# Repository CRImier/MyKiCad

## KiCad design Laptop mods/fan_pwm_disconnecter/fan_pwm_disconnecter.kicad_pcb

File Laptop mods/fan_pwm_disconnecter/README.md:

# Laptop fan PWM disconnecter

This is a board that allows you to run your laptop fans at full speed.
It is controlled by either a slide switch (included) or a toggle button..

It should be compatible with any kind of fan pinout. It has a slide switch attached that lets you test it the board,
and the switch board breaks off so you can place it somewhere where the switch will be accessible to you without disassembly,
using just two wires.

How to add this board to your laptop:

1) find out your fan's pinout. It's going to have 4 pins:
    - GND: ground
    - VCC: power
    - SENS: fan RPM signal output. We're not interested in this pin, it should just be passed through.
    - PWM: signal for fan speed control
2) jumper two-pin pads on the back that correspond to GND, VCC and SENS on the pinout. Leave the PWM pins un-jumpered.
3) connect the GND pad to the GND jumper pads
4) connect the VCC pad to the VCC jumper pads
5) connect the input PWM pad to the PWM jumper input pad
6) connect the output PWM pad to the PWM jumper output pad
7) Plug the fan into the board and plug the board into your laptop's motherboard
8) Test that everything works as intended
9) Break away the switch PCB
10) Position and fasten the main board inside the laptop's case - insulate the board with kapton tape, use double-sided tape or hotglue as needed
11) Position and fasten the switch board inside the laptop's case, the same way. You can put it e.g. under the RAM/HDD cover or behind the Kensington lock plate.
12) Use wires to connect the slide switch to the switch connector on the top of the board.

This repository also includes files for manufacturing a 2x9 panel.
Signal names are silkscreened on the board's bottom layer.

- PCB size: 36.25mm*8.25mm
- Layer count: 2

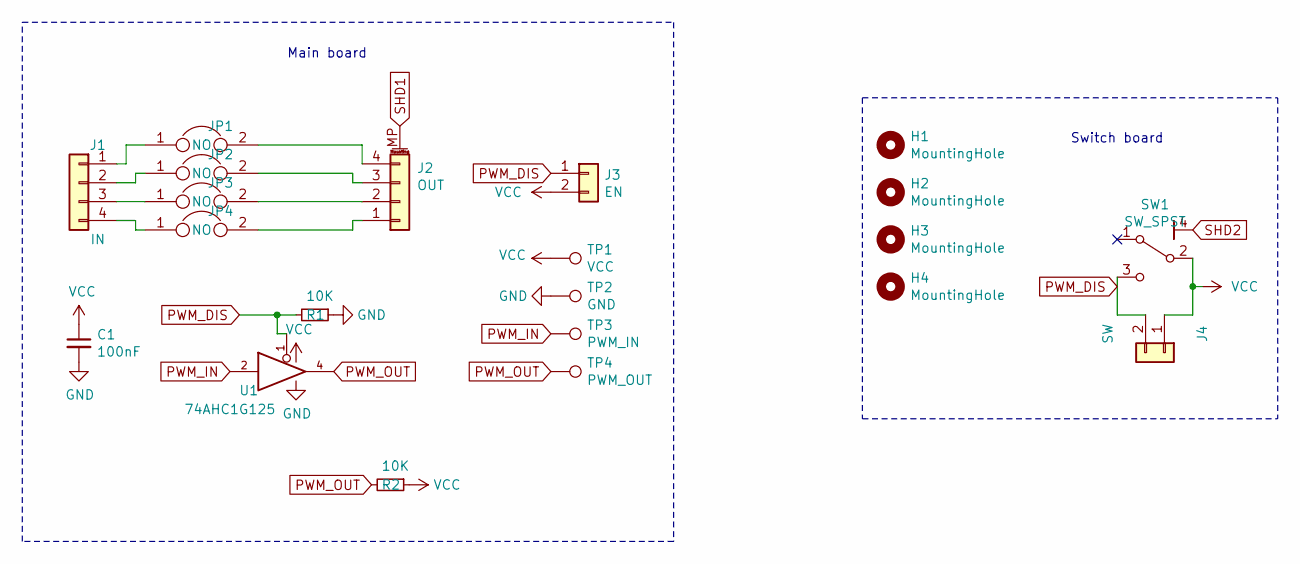
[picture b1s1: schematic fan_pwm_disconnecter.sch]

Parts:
C1: 100nF; C_0805_2012Metric_Pad1.15x1.40mm_HandSolder
H1, H2, H3, H4: MountingHole; MountingHole_2mm
J1: IN; PinHeader_1x04_P2.00mm_Vertical
J2: OUT; JST_SH_SM04B-SRSS-TB_1x04-1MP_P1.00mm_Horizontal
J3: EN; PinHeader_1x02_P2.00mm_Vertical
J4: SW; PinHeader_1x04_P2.00mm_Vertical
JP1, JP2, JP3, JP4: NO; SolderJumper-2_P1.3mm_Open_Pad1.0x1.0mm
R1, R2: 10K; R_0805_2012Metric_Pad1.15x1.40mm_HandSolder
SW1: SW_SPST; SW_SPDT_PCM12
TP1: VCC; TestPoint_Pad_1.0x1.0mm
TP2: GND; TestPoint_Pad_1.0x1.0mm
TP3: PWM_IN; TestPoint_Pad_1.0x1.0mm
TP4: PWM_OUT; TestPoint_Pad_1.0x1.0mm
U1: 74AHC1G125; SOT-353_SC-70-5_Handsoldering

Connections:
GND: C1.2, R1.1, TP2.1, U1.3 (GND)
unnamed: J1.1, JP1.1
unnamed: J1.2, JP2.1
unnamed: J1.3, JP3.1
unnamed: J1.4, JP4.1
unnamed: J2.1, JP4.2
unnamed: J2.2, JP3.2
unnamed: J2.3, JP2.2
unnamed: J2.4, JP1.2
PWM_DIS: J3.1, J4.2, R1.2, SW1.3 (C), U1.1
PWM_IN: TP3.1, U1.2
PWM_OUT: R2.2, TP4.1, U1.4
SHD1: J2.MP (MountPin)
SHD2: SW1.4 (SHD)
VCC: C1.1, J3.2, J4.1, R2.1, SW1.2 (B), TP1.1, U1.5 (VCC)

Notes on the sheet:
Main board
Switch board

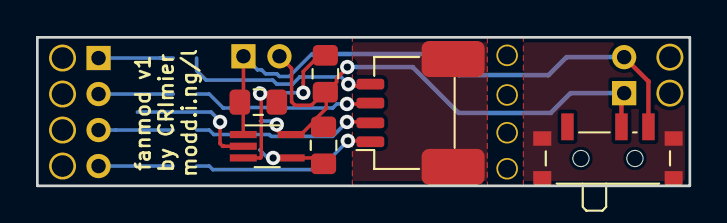
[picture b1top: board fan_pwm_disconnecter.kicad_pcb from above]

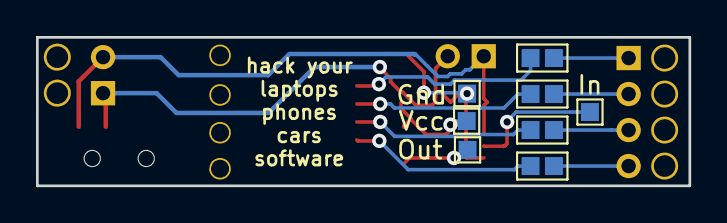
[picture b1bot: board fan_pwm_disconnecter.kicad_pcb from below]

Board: 2 copper layers, 36.2 x 8.2 mm, 21 parts (8 on the bottom side), 13 nets.

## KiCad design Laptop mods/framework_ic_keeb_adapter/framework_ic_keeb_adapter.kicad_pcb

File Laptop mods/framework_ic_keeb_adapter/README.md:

# Framework input shim
This is a small shim for the Framework laptop motherboard or input controller.
It is meant to plug directly into a motherboard or an input controller, 
and you can connect your peripherals to it.

it exposes basically everything it can - keyboard, keyboard backlight and fingerprint
sensor, compliant with the pinout of these .
It also exposes a USB port header with 5V power (2.54mm),
pin headers with power switch (2.54mm), touchpad (2.54mm),
keyboard backlight (2mm), Caps Lock (2mm) and fingerprint LED (1.27mm) connections.

The top part is designed to fit inside the outline of the input connector FPC plug,
within the motherboard outline, so that it can easily be added to existing designs.
All the other connections extend beyond the mainboard outline.

For wire connections, this shim uses THT holes, since it's relatively easy to rip
an SMD pad off the board by pulling on a wire.

Markings on the PCB: "FrmW input breakout"

## Notes

- Signal names are silkscreened on the board's bottom layers.
- This board is untested and there's no guarantees of fitness.
- I recommend a stencil for assembling this board.

## Info

- Software: Kicad 7
- Version: 1
- PCB size: 38.7x15.6
- Layer count: 2

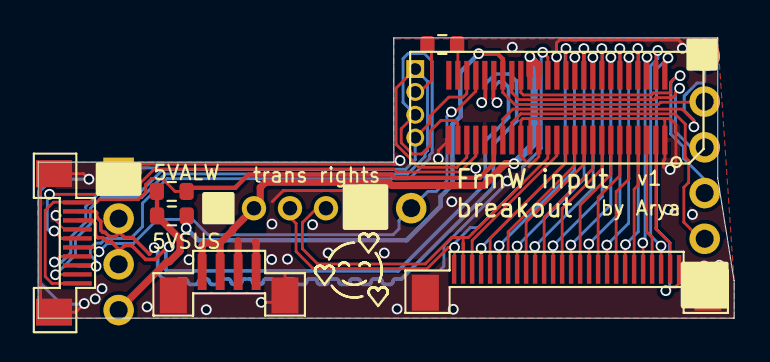
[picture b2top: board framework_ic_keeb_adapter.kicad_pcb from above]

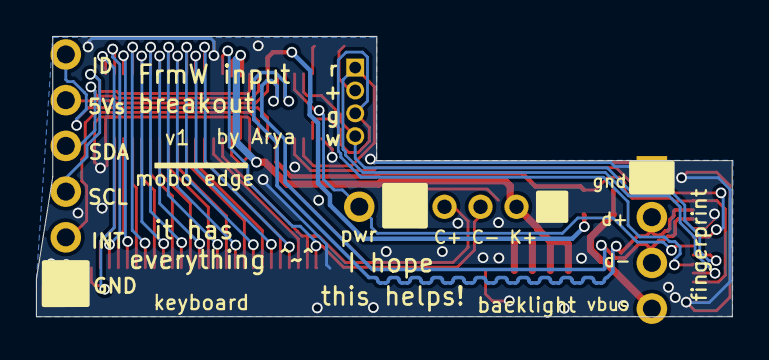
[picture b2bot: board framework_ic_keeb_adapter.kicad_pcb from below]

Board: 2 copper layers, 38.7 x 15.6 mm, 12 parts (5 on the bottom side), 44 nets.

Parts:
J1: FPR_LED; PinHeader_1x04_P1.27mm_Vertical
J2: fpc_input_conn; Amphenol_10156001
J3: PWRSW; PinHeader_1x02_P2.54mm_Vertical
J4: USB; PinHeader_1x04_P2.54mm_Vertical
J5: KnC; PinHeader_1x04_P2.00mm_Vertical
J6: KB; FPC_26
J7: BL; FPC_4
J8: TOUCH; PinHeader_1x06_P2.54mm_Vertical
J9: FPR; FPC_10
R1: 0R; R_0603_1608Metric
R2: NC; R_0603_1608Metric
R3: 560R; R_0603_1608Metric

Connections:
/5VALW: J2.31, J9.1, J9.10, R2.2
/5VS: J2.19, J8.5, R1.1
/CAPS_N: J2.14, J5.3, J6.1
/CAPS_P_5V: J2.37, J5.4, J6.2
/FPR_CTRL: J2.29, J9.5
/FPR_LED_COM_5V: J2.24, R3.1
/FPR_LED_G: J1.3, J2.27, J9.8
/FPR_LED_R: J1.1, J2.28, J9.9
/FPR_LED_W: J1.4, J2.23, J9.7
/KBL_P: J2.15, J2.16, J5.2, J7.1, J7.2
/KSI0: J2.1, J6.26
/KSI1: J2.49, J6.25
/KSI2: J2.2, J6.24
/KSI3: J2.48, J6.23
/KSI4: J2.3, J6.22
/KSI5: J2.47, J6.21
/KSI6: J2.4, J6.20
/KSI7: J2.46, J6.19
/KSO0: J2.5, J6.18
/KSO1: J2.45, J6.17
/KSO2: J2.6, J6.16
/KSO3: J2.44, J6.15
/KSO4: J2.7, J6.14
/KSO5: J2.43, J6.13
/KSO6: J2.8, J6.12
/KSO7: J2.42, J6.11
/KSO8: J2.9, J6.10
/KSO9: J2.41, J6.9
/KSO10: J2.10, J6.8
/KSO11: J2.40, J6.7
/KSO12: J2.11, J6.6
/KSO13: J2.39, J6.5
/KSO14: J2.12, J6.4
/KSO15: J2.38, J6.3
/SWITCH: J2.22, J3.2, J9.6
/TP_BOARD_ID: J2.32, J8.6
/TP_INT: J2.33, J8.2
/TP_SCL: J2.17, J8.3
/TP_SDA: J2.18, J8.4
/USB_N: J2.20, J4.3, J9.3
/USB_P: J2.21, J4.2, J9.2
/VBUS: J4.4, R1.2, R2.1
GND: J2.13, J2.26, J2.30, J2.34, J2.35, J2.36, J2.50, J3.1, J4.1, J5.1, J6.MP (MountPin), J7.3, J7.4, J7.MP (MountPin), J8.1, J9.4, J9.MP (MountPin)
unnamed: J1.2, R3.2

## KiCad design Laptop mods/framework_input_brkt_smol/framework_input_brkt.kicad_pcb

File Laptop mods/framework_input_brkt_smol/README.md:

# Framework input shim

This is a small shim for the Framework laptop motherboard. It exposes the power button,
a USB port with 5V power, keyboard backlight, Caps Lock and fingerprint LED connections.
It is designed to fit inside the outline of the input connector FPC plug,
within the motherboard outline, so that it can easily be added to existing designs.

For wire connections, this shim uses THT holes, since it's relatively easy to rip
an SMD pad off the board by pulling on a wire. This [requires some kapton fixes](https://twitter.com/FairywrenTech/status/1559150268557795331)
during assembly, however.

Markings on the PCB: "FrmW input brkt" (shortened because the board has to be very small)

Connector used: Amphenol 10156001-051100LF

These are KiCad 5 files - will be updated to KiCad 6 sometime later.

#Changes in v3:

- Updated to KiCad 6
- Updated soldermask on connector soldering layer to decrease chances of THT-to-connector shorts
- Cosmetic: removed between-pin traces on a GND group of pins
- Adjusted traces so that there's less visual "shorts"

# Changes in v2: 

The input connector symbol numbering was incorrect
and v1 of this adapter could break your mobo or something.

- Signal names are silkscreened on the board's top layers.

- Software: Kicad 6
- Version: 2
- PCB size: 18x7.75
- Layer count: 2

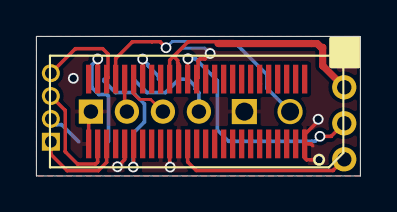
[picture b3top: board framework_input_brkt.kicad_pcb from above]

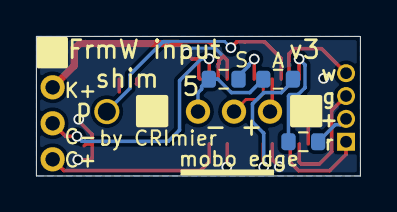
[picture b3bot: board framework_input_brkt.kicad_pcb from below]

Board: 2 copper layers, 18.0 x 7.8 mm, 8 parts (7 on the bottom side), 15 nets.

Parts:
J1: FPR_LED; PinHeader_1x04_P1.27mm_Vertical
J2: fpc_input_conn; Amphenol_10156001
J3: PWRSW; PinHeader_1x02_P2.54mm_Vertical
J4: USB; PinHeader_1x04_P2.00mm_Vertical
J5: KnC; PinHeader_1x04_P2.00mm_Vertical
R1: 0R; R_0603_1608Metric
R2: NC; R_0603_1608Metric
R3: 560R; R_0603_1608Metric

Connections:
/5VALW: J2.31, R2.2
/5VS: J2.19, R1.1
/CAPS_N: J2.14, J5.3
/CAPS_P_5V: J2.37, J5.4
/FPR_LED_COM_5V: J2.24, R3.1
/FPR_LED_G: J1.3, J2.27
/FPR_LED_R: J1.1, J2.28
/FPR_LED_W: J1.4, J2.23
/KBL_P: J2.15, J2.16, J5.2
/SWITCH: J2.22, J3.2
/USB_N: J2.20, J4.3
/USB_P: J2.21, J4.2
GND: J2.13, J2.26, J2.30, J2.34, J2.35, J2.36, J2.50, J3.1, J4.1, J5.1
unnamed: J1.2, R3.2
unnamed: J4.4, R1.2, R2.1
